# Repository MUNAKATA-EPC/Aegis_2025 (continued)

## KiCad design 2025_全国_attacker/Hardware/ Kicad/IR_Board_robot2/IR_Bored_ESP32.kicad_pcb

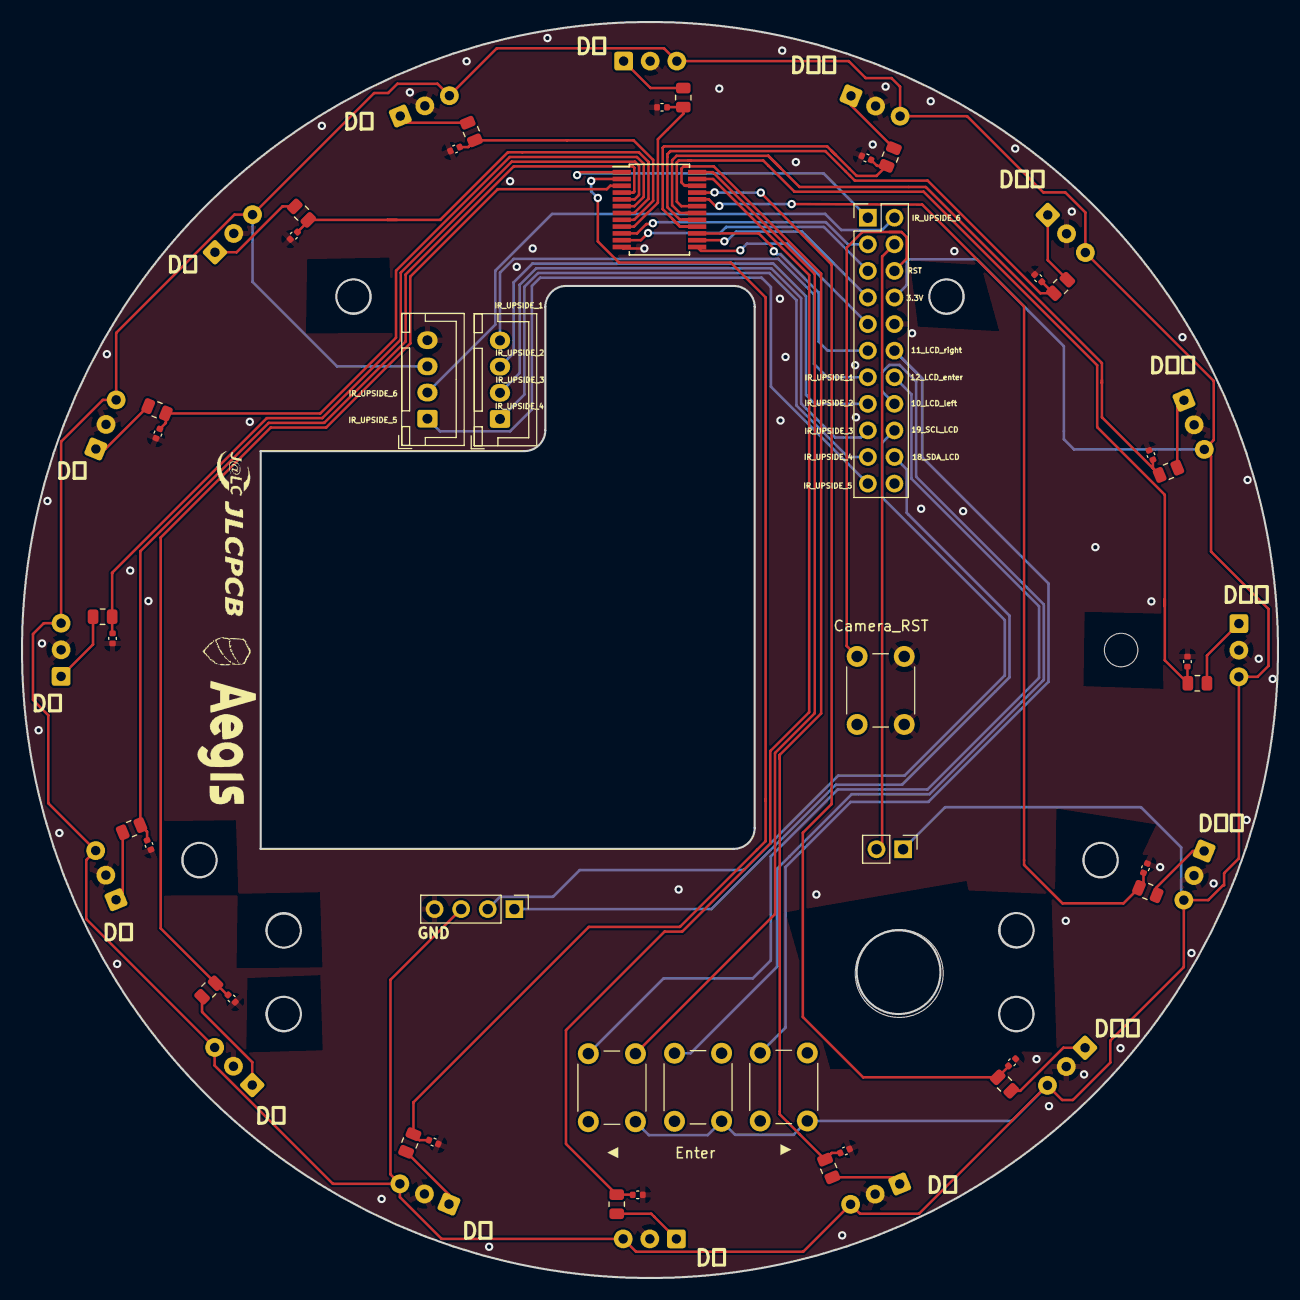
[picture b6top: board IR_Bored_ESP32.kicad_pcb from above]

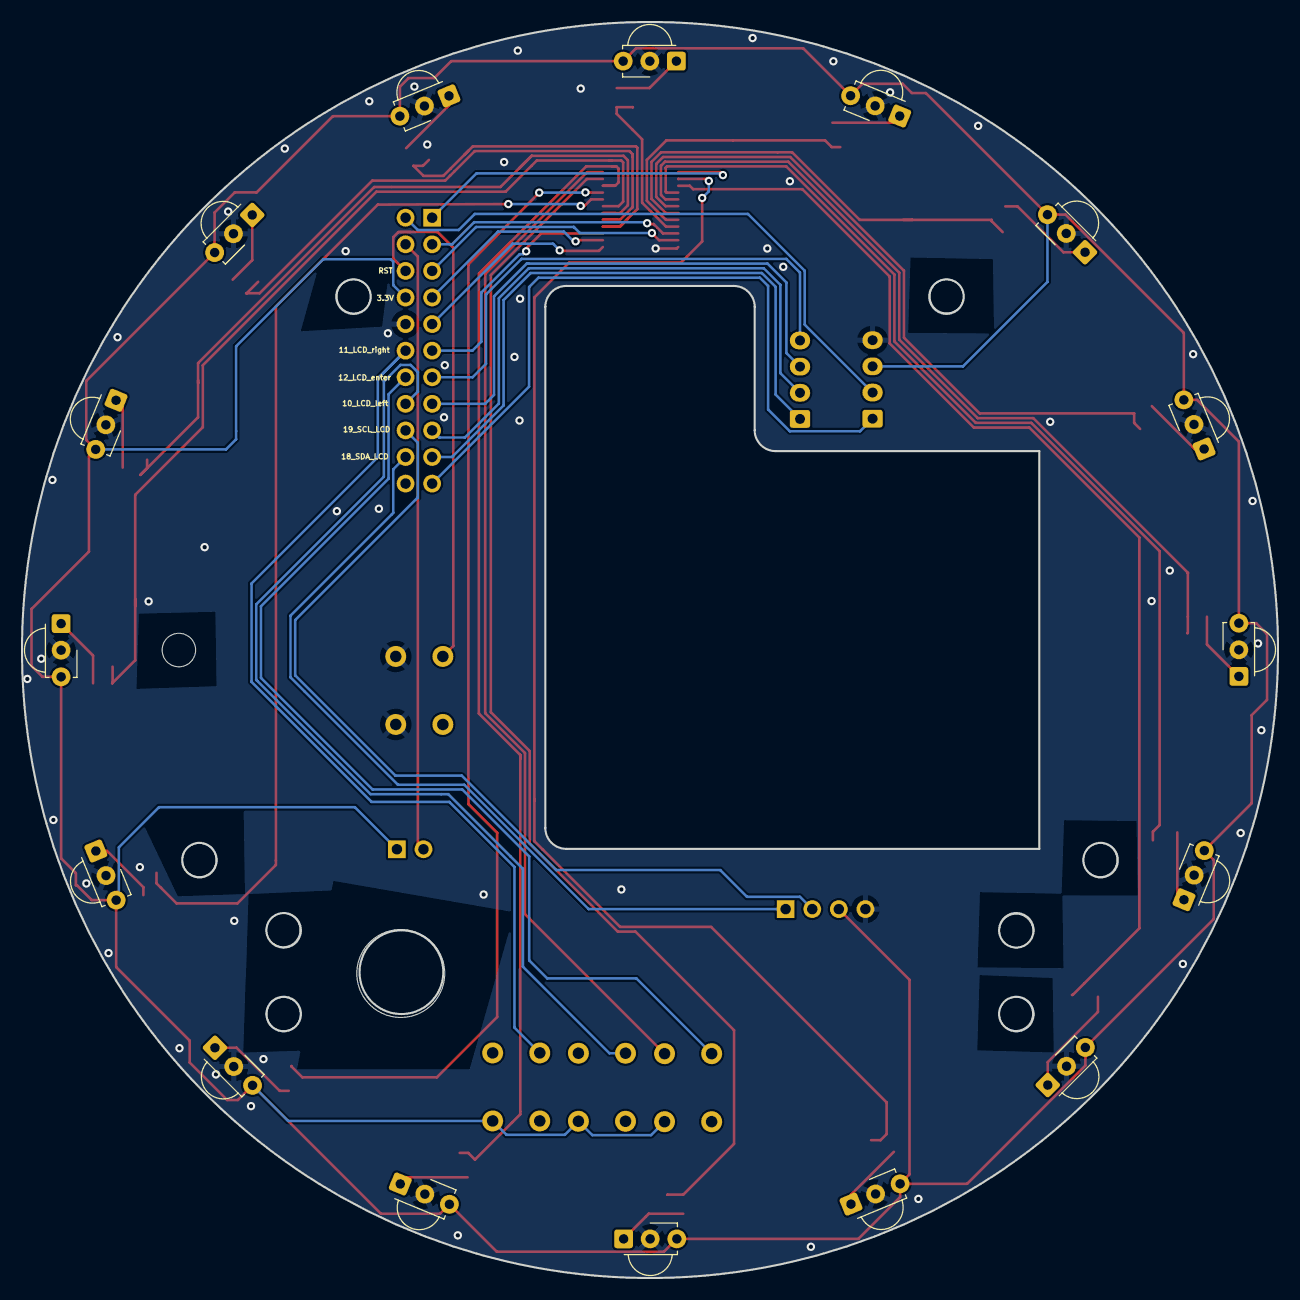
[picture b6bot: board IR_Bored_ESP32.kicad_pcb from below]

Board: 2 copper layers, 120.0 x 120.0 mm, 58 parts (16 on the bottom side), 53 nets.

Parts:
C1, C2, C3, C4, C5, C6, C7, C8, C9, C10, C11, C12, C13, C14, C15, C16: 104; C_0402_1005Metric
Camera_RST: SW_DIP_x01; SW_PUSH_6mm_H5mm
J1: Conn_01x04_Socket; PinHeader_1x04_P2.54mm_Vertical
J2, J3: Conn_01x04_Pin; JST_XH_B4B-XH-A_1x04_P2.50mm_Vertical
J4: Conn_02x11_Odd_Even; PinHeader_2x11_P2.54mm_Vertical
R1, R2, R3, R4, R5, R6, R7, R8, R9, R10, R11, R12, R13, R14, R15, R16: 22k; R_0805_2012Metric
SW1, SW2, SW3: LCD; SW_PUSH_6mm_H5mm
SW5: SW_DIP_x01; PinHeader_1x02_P2.54mm_Vertical
U1, U2, U3, U4, U5, U6, U7, U8, U9, U10, U11, U12, U13, U14, U15, U17: TSSP58P38; Vishay_MINICAST-3Pin
U16: CD74HC4067SM; SSOP-24_5.3x8.2mm_P0.65mm

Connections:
+3.3V: J1.3, J3.3, J4.8, SW1.2, SW2.2, SW3.2, SW5.1, U1.3 (Vs), U2.3 (Vs), U3.3 (Vs), U4.3 (Vs), U5.3 (Vs), U6.3 (Vs), U7.3 (Vs), U8.3 (Vs), U9.3 (Vs), U10.3 (Vs), U11.3 (Vs), U12.3 (Vs), U13.3 (Vs), U14.3 (Vs), U15.3 (Vs), U16.24 (VCC), U17.3 (Vs)
D0: C3.1, R3.1, U16.9 (I0)
D1: C4.1, R4.1, U16.8 (I1)
D2: C1.1, R1.1, U16.7 (I2)
D3: C2.1, R2.1, U16.6 (I3)
D4: C5.1, R5.1, U16.5 (I4)
D5: C6.1, R6.1, U16.4 (I5)
D6: C7.1, R7.1, U16.3 (I6)
D7: C8.1, R8.1, U16.2 (I7)
D8: C11.1, R11.1, U16.23 (I8)
D9: C12.1, R12.1, U16.22 (I9)
D10: C9.1, R9.1, U16.21 (I10)
D11: C10.1, R10.1, U16.20 (I11)
D12: C13.1, R13.1, U16.19 (I12)
D13: C14.1, R14.1, U16.18 (I13)
D14: C15.1, R15.1, U16.17 (I14)
D15: C16.1, R16.1, U16.16 (I15)
Data_IR_sensor: J4.1, U16.1 (COM)
E: J4.11, U16.15 (~E)
GND: C1.2, C2.2, C3.2, C4.2, C5.2, C6.2, C7.2, C8.2, C9.2, C10.2, C11.2, C12.2, C13.2, C14.2, C15.2, C16.2, Camera_RST.2, J1.4, J3.4, J4.10, U1.2 (GND), U2.2 (GND), U3.2 (GND), U4.2 (GND), U5.2 (GND), U6.2 (GND), U7.2 (GND), U8.2 (GND), U9.2 (GND), U10.2 (GND), U11.2 (GND), U12.2 (GND), U13.2 (GND), U14.2 (GND), U15.2 (GND), U16.12 (GND), U17.2 (GND)
IR_Data1_Upside: J2.4, J4.13
IR_Data2_Upside: J2.3, J4.15
IR_Data3_Upside: J2.2, J4.17
IR_Data4_Upside: J2.1, J4.19
IR_Data5_Upside: J3.1, J4.21
IR_Data6_Upside: J3.2, J4.2
IRout0: R3.2, U17.1 (OUT)
IRout1: R4.2, U1.1 (OUT)
IRout2: R1.2, U2.1 (OUT)
IRout3: R2.2, U3.1 (OUT)
IRout4: R5.2, U4.1 (OUT)
IRout5: R6.2, U5.1 (OUT)
IRout6: R7.2, U6.1 (OUT)
IRout7: R8.2, U7.1 (OUT)
IRout8: R11.2, U8.1 (OUT)
IRout9: R12.2, U9.1 (OUT)
IRout10: R9.2, U10.1 (OUT)
IRout11: R10.2, U11.1 (OUT)
IRout12: R13.2, U12.1 (OUT)
IRout13: R14.2, U13.1 (OUT)
IRout14: R15.2, U14.1 (OUT)
IRout15: R16.2, U15.1 (OUT)
LCD-TeensyD10: J4.12, SW3.1
LCD-TeensyD11: J4.14, SW1.1
LCD-TeensyD12: J4.16, SW2.1
RST: Camera_RST.1, J4.6
S0: J4.3, U16.10 (S0)
S1: J4.5, U16.11 (S1)
S2: J4.7, U16.14 (S2)
S3: J4.9, U16.13 (S3)
SCL_LCD: J1.2, J4.18
SDA_LCD: J1.1, J4.20
Start_switch: J4.4, SW5.2

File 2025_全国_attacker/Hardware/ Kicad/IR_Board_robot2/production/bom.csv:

Designator,Footprint,Quantity,Value,LCSC Part #
"C1, C10, C11, C12, C13, C14, C15, C16, C2, C3, C4, C5, C6, C7, C8, C9",0402,16,104,
CAMERA_RST,SW_PUSH_6mm_H5mm,1,SW_DIP_x01,
J1,PinHeader_1x04_P2.54mm_Vertical,1,Conn_01x04_Socket,
"J2, J3",JST_XH_B4B-XH-A_1x04_P2.50mm_Vertical,2,Conn_01x04_Pin,
J4,PinHeader_2x11_P2.54mm_Vertical,1,Conn_02x11_Odd_Even,
"R1, R10, R11, R12, R13, R14, R15, R16, R2, R3, R4, R5, R6, R7, R8, R9",0805,16,22k,
"SW1, SW2, SW3",SW_PUSH_6mm_H5mm,3,LCD,
SW5,PinHeader_1x02_P2.54mm_Vertical,1,SW_DIP_x01,
"U1, U10, U11, U12, U13, U14, U15, U17, U2, U3, U4, U5, U6, U7, U8, U9",Vishay_MINICAST-3Pin,16,TSSP58P38,
U16,SSOP-24_5.3x8.2mm_P0.65mm,1,CD74HC4067SM,

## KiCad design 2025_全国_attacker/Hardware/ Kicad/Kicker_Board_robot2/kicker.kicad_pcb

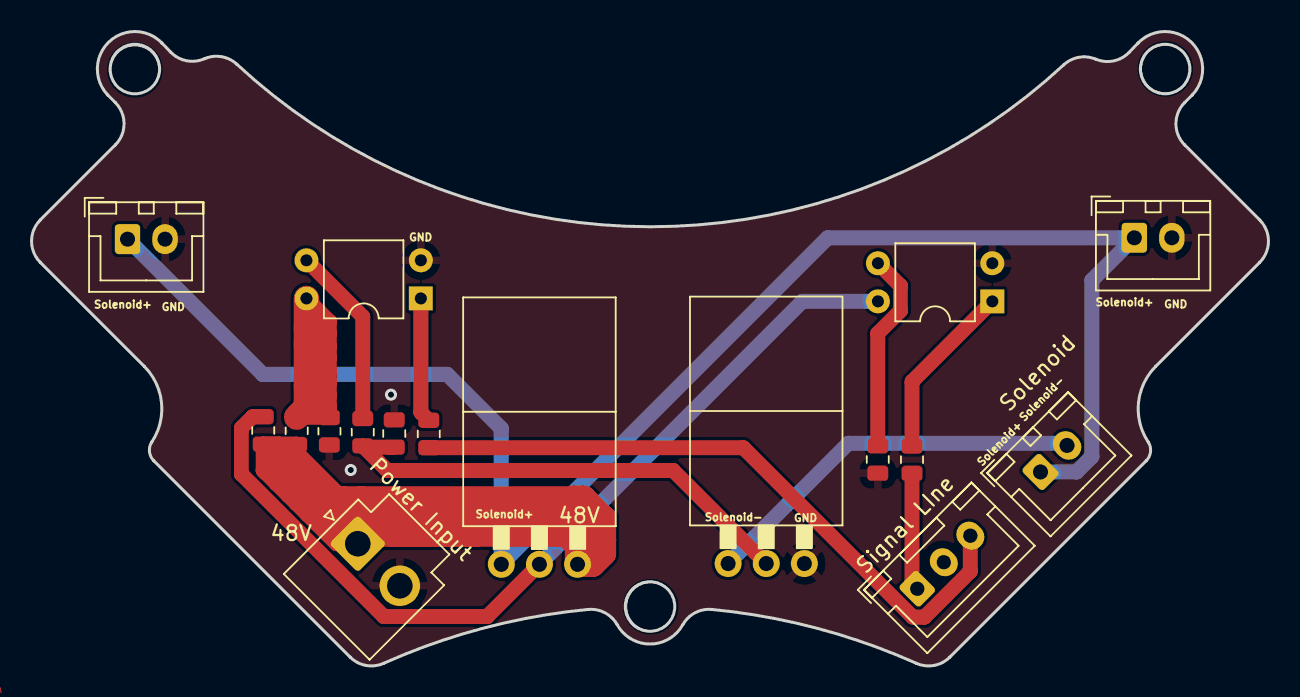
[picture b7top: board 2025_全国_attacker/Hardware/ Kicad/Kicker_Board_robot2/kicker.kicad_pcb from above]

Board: 2 copper layers, 82.4 x 42.3 mm, 17 parts (0 on the bottom side), 13 nets.

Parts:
C1, C2: C; JST_XH_B2B-XH-A_1x02_P2.50mm_Vertical
J1: Conn_01x02_Socket; JST_VH_B2P-VH_1x02_P3.96mm_Vertical
J3: Conn_01x03_Socket; JST_XH_B3B-XH-A_1x03_P2.50mm_Vertical
J4: Conn_01x02_Socket; JST_XH_B2B-XH-A_1x02_P2.50mm_Vertical
Q1: PMOS; K15A20D
Q3: NMOS; K15A20D
R1, R3, R8: 330K; R_0805_2012Metric
R2, R9: 1K; R_0805_2012Metric
R4: 10K; R_0805_2012Metric
R6, R7: 2K; R_0805_2012Metric
U1, U2: EL817; DIP-4_W7.62mm

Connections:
+15V: R7.2, R9.1, U2.4
+48V: J1.1, Q1.3 (S), R2.1, R7.1
FET1: J3.1, R1.1
FET２: J3.3, R8.1
GND: C1.2, C2.2, J1.2, J3.2, Q3.3 (S), R4.2, R6.2, R9.2, U1.2, U2.2
unnamed: Q1.2 (G), R2.2, U1.4
unnamed: Q3.2 (G), R3.1, R4.1
unnamed: R1.2, U1.1
unnamed: R3.2, U2.3
unnamed: R6.1, U1.3
unnamed: R8.2, U2.1
Solenoid+: C1.1, C2.1, J4.1, Q1.1 (D)
Solenoid-: J4.2, Q3.1 (D)

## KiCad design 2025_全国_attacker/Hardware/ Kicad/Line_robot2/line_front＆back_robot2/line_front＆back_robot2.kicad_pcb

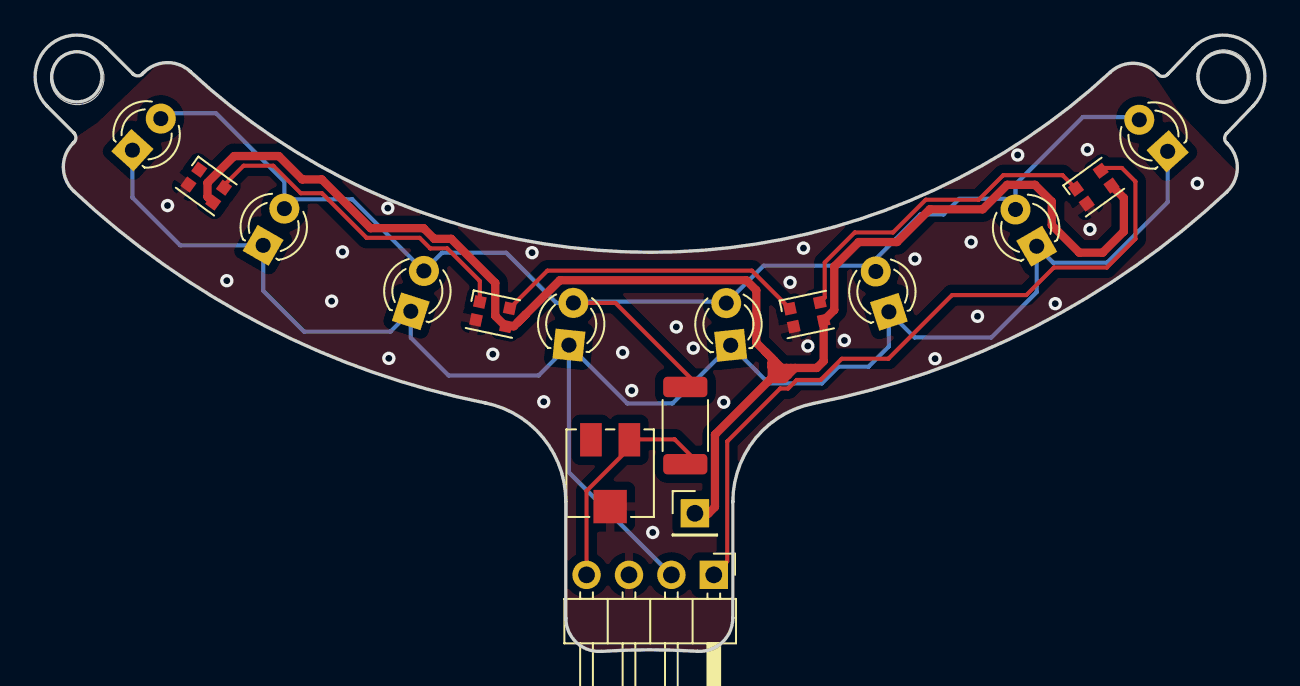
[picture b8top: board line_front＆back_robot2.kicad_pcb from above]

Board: 2 copper layers, 73.6 x 36.9 mm, 16 parts (0 on the bottom side), 9 nets.

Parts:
D1, D2, D3, D5: NeoPixel_THT; LED_WS2812B-2020_PLCC4_2.0x2.0mm
J2: Conn_01x04_Pin; PinHeader_1x04_P2.54mm_Horizontal
J3: Conn_01x01_Pin; PinHeader_1x01_P2.54mm_Vertical
Q1, Q2, Q3, Q4, Q7, Q8, Q9, Q10: Q_Photo_NPN; LED_D3.0mm_Clear
R8: 1K; R_2010_5025Metric
RV2: R_Potentiometer_Trim_US; Potentiometer_Vishay_TS53YJ_Vertical

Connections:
+3.3V: J2.2, Q1.1 (C), Q2.1 (C), Q3.1 (C), Q4.1 (C), Q7.1 (C), Q8.1 (C), Q9.1 (C), Q10.1 (C)
+5V: D1.3 (VDD), D2.3 (VDD), D3.3 (VDD), D5.3 (VDD), J3.1
/PWM: D3.4 (DIN), J2.1
/S: J2.4, R8.1, RV2.3
GND: D1.2 (GND), D2.2 (GND), D3.2 (GND), D5.2 (GND), J2.3, RV2.2
unnamed: D1.4 (DIN), D5.1 (DOUT)
unnamed: D2.4 (DIN), D3.1 (DOUT)
unnamed: D2.1 (DOUT), D5.4 (DIN)
unnamed: Q1.2 (E), Q2.2 (E), Q3.2 (E), Q4.2 (E), Q7.2 (E), Q8.2 (E), Q9.2 (E), Q10.2 (E), R8.2
